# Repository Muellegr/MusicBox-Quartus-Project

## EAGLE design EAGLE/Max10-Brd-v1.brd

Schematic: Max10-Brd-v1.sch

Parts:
C1: 0.1uF; C0805
C2, C3: 4pF; C0805
C4, C15, C16, C32: 0.01uF; C0805
C5: 1nF; C0805
C6, C8, C11, C13: 10uF; C0805
C7, C9, C12, C14, C21, C24, C27, C30: 1uF; C0805
C10, C19, C22, C25, C28: 4.7uF; C0805
C17: 100uF; E5-6
C18: 1000uF; E3,5-10
C20, C23, C26, C29: 10nF; C0805
C31: 0.47uF; C0805
CB: 1uF; C0805
CI: 0.39uF; C0805
CS: 1uF Tant; C050-075X075
D1: DIODE-DO201-15; DO201-15
FB1, FB6: 220; M0805
FB2, FB3, FB4, FB5: 30; M0805
IC1: INA332AIDGKR; SOP65P490X110-8N
IC2: LM4991MAX_NOPB; SOIC127P600X175-8N
IC3: 10M50DAF484C7G; BGA484C100P22X22_2300X2300X200
IC5: IS42S16400J-7TLI; SOP80P1176X120-54N
IC6: CDCE937PWRG4; SOP65P640X120-20N
IC7: AD5320BRTZ; SOT95P280X145-6N
IC8: ADS7868IDBVR; SOT95P280X145-6N
IC9, IC10, IC11, IC12: MCP1726T-ADJE_SN; SOIC127P600X175-8N
IC13: REF3125AQDBZRQ1; SOT95P237X112-3N
IC14: LM2576HVS-ADJ; KTT0005B
J1: 1X2-3.5MM
J2, J14: CONN_05X2SHD; 2X5-SHROUDED
J3: CONN_20X2SHROUDED; 2X20_SHROUDED
J4, J5, J6, J7, J8: CONN_02; 1X02
J9, J10: CONN_01; 1X01
J11, J12, J13: CONN_03; 1X03
L1: 100uH; INDPM125125X650N
LED1: LED3MM
Q1: ELECTRET; 9.7ELECTRET
Q2: 24MHz; CTS406
R1, R2: 20k; M0805
R4, R5, R6: 2.2k; M0805
R8, R9, R10, R11, R12, R13, R14: 4.7k; M0805
R15, R16, R17: 18.2; M0805
R18, R19: 10k; M0805
R21: 1k; M0805
R22: 220; R0805
R23, R26: 510k; R0805
R24: 100k; R0805
R25: 150k; R0805
R27: 86k; R0805
R28: 12k; R0805
R29: 40k; R0805
R30: 20k; R0805
R31, R32: 0.4; M0805
TP$1: TEST_POINT
U$1: 2.1MMJACKTHM; PJ-102A
VR1: 10k; TRIMPOT-PTH-3386U

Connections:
ADC_CLK_10: IC3.N5 (IO_194), J13.3, R17.2
ADC_VREF: C6.1, C7.1, FB2.2, IC3.H6 (ADC_VREF)
AMP_MIC_OUT: IC1.6 (VOUT), IC8.3 (VIN), J10.1, R6.2
AUD_IN: C32.1, CI.2, IC7.1 (VOUT), J9.1
CS_N_ADC: IC3.W1 (IO_280), IC8.6 (CS), J12.1
DIN_DAC: IC3.E22 (IO_97), IC7.4 (DIN), J11.3
DRAM_ADDR0: IC3.U17 (IO_255), IC5.23 (A0)
DRAM_ADDR1: IC3.W19 (IO_298), IC5.24 (A1)
DRAM_ADDR2: IC3.V18 (IO_276), IC5.25 (A2)
DRAM_ADDR3: IC3.U18 (IO_256), IC5.26 (A3)
DRAM_ADDR4: IC3.U19 (IO_257), IC5.29 (A4)
DRAM_ADDR5: IC3.T18 (IO_242), IC5.30 (A5)
DRAM_ADDR6: IC3.T19 (IO_243), IC5.31 (A6)
DRAM_ADDR7: IC3.R18 (IO_234), IC5.32 (A7)
DRAM_ADDR8: IC3.P18 (IO_216), IC5.33 (A8)
DRAM_ADDR9: IC3.P19 (IO_217), IC5.34 (A9)
DRAM_ADDR10: IC3.R22 (IO_236), IC3.T20 (IO_244), IC5.22 (A10)
DRAM_ADDR11: IC3.P20 (IO_218), IC5.35 (A11)
DRAM_ADDR12: IC3.R20 (IO_235), IC5.36 (NC_1)
DRAM_BA0: IC3.T21 (IO_245), IC5.20 (BA0)
DRAM_BA1: IC3.T22 (IO_246), IC5.21 (BA1)
DRAM_CAS_N: IC3.U21 (IO_259), IC5.17 (!CAS), R10.2
DRAM_CKE: IC3.N22 (IO_203), IC5.37 (CKE), R12.2
DRAM_CLK: IC3.L14 (IO_171), IC5.38 (CLK)
DRAM_CS_N: IC3.U20 (IO_258), IC5.19 (!CS), R8.2
DRAM_DQ0: IC3.Y21 (IO_318), IC5.2 (DQ0)
DRAM_DQ1: IC3.Y20 (IO_317), IC5.4 (DQ1)
DRAM_DQ2: IC3.AA22 (IO_339), IC5.5 (DQ2)
DRAM_DQ3: IC3.AA21 (IO_338), IC5.7 (DQ3)
DRAM_DQ4: IC3.Y22 (IO_319), IC5.8 (DQ4)
DRAM_DQ5: IC3.W22 (IO_300), IC5.10 (DQ5)
DRAM_DQ6: IC3.W20 (IO_299), IC5.11 (DQ6)
DRAM_DQ7: IC3.V21 (IO_278), IC5.13 (DQ7)
DRAM_DQ8: IC3.P21 (IO_219), IC3.P22 (IO_220), IC5.42 (DQ8)
DRAM_DQ9: IC3.J22 (IO_151), IC5.44 (DQ9)
DRAM_DQ10: IC3.H21 (IO_135), IC5.45 (DQ10)
DRAM_DQ11: IC3.H22 (IO_136), IC5.47 (DQ11)
DRAM_DQ12: IC3.G22 (IO_121), IC5.48 (DQ12)
DRAM_DQ13: IC3.G20 (IO_120), IC5.50 (DQ13)
DRAM_DQ14: IC3.G19 (IO_119), IC5.51 (DQ14)
DRAM_DQ15: IC3.F22 (IO_112), IC5.53 (DQ15)
DRAM_LDQM: IC3.V22 (IO_279), IC5.15 (LDQM)
DRAM_RAS_N: IC3.U22 (IO_260), IC5.18 (!RAS), R9.2
DRAM_UDQM: IC3.J21 (IO_150), IC5.39 (UDQM)
DRAM_WE_N: IC3.V20 (IO_277), IC5.16 (!WE), R11.2
GND: C2.1, C3.1, C4.2, C5.2, C6.2, C7.2, C8.2, C9.2, C10.2, C11.2, C12.2, C13.2, C14.2, C15.2, C16.2, C17.-, C18.-, C19.2, C20.2, C21.2, C22.2, C23.2, C24.2, C25.2, C26.2, C27.2, C28.2, C29.2, C30.2, C31.2, C32.2, CB.2, CS.2, D1.A, IC1.2 (VIN-), IC1.4 (V-), IC1.8 (SHUTDOWN), IC2.1 (SHUTDOWN), IC2.7 (GND), IC3.A1 (GND_1), IC3.A22 (GND_2), IC3.AA4 (GND_55), IC3.AA18 (GND_56), IC3.AB1 (GND_57), IC3.AB22 (GND_58), IC3.B6 (GND_3), IC3.B9 (GND_4), IC3.B13 (GND_5), IC3.B18 (GND_6), IC3.D4 (GND_7), IC3.D11 (GND_8), IC3.D16 (GND_9), IC3.D20 (GND_10), IC3.E2 (GND_11), IC3.E5 (NC_1), IC3.E7 (GND_12), IC3.F6 (NC_2), IC3.F8 (IO_104), IC3.F10 (GND_13), IC3.F13 (GND_14), IC3.G5 (ANAIN1), IC3.G6 (GND_15), IC3.G8 (GND_16), IC3.G15 (GND_17), IC3.G18 (GND_18), IC3.G21 (GND_19), IC3.H5 (REFGND), IC3.J2 (GND_20), IC3.J5 (ANAIN2), IC3.J6 (GND_21), IC3.J16 (GND_22), IC3.J19 (GND_23), IC3.K3 (GND_24), IC3.K10 (GND_25), IC3.K12 (GND_26), IC3.L5 (GND_27), IC3.L13 (GND_28), IC3.L17 (GND_29), IC3.L21 (GND_30), IC3.M7 (GND_31), IC3.M10 (GND_32), IC3.M16 (GND_33), IC3.M19 (GND_34), IC3.N11 (GND_35), IC3.N13 (GND_36), IC3.P2 (GND_37), IC3.P6 (GND_38), IC3.P17 (GND_39), IC3.R19 (GND_40), IC3.R21 (GND_41), IC3.T4 (GND_42), IC3.T8 (GND_43), IC3.T14 (GND_44), IC3.T16 (GND_45), IC3.U10 (GND_46), IC3.U13 (GND_47), IC3.V2 (GND_48), IC3.V6 (GND_49), IC3.V19 (GND_50), IC3.W21 (GND_51), IC3.Y9 (GND_52), IC3.Y12 (GND_53), IC3.Y15 (GND_54), IC5.6 (GNDQ_1), IC5.12 (GND_1), IC5.28 (GND_2), IC5.41 (GND_3), IC5.46 (GNDQ_2), IC5.52 (GND_4), IC5.54 (GND_5), IC6.5 (GND_1), IC6.9 (GND_2), IC6.16 (GND_3), IC7.2 (GND), IC8.2 (GND), IC9.4 (GND), IC10.4 (GND), IC11.4 (GND), IC12.4 (GND), IC13.3 (GND), IC14.3 (GND_1), IC14.5 (!ON!/OFF), IC14.6 (GND_2), J2.2, J2.10, J4.2, J5.2, J6.2, J7.2, J8.2, LED1.K (C), Q1.- (1), R21.2, R24.1, R25.1, R28.1, R30.1, TP$1.TP1, U$1.RING, U$1.RING_SW, VR1.3 (CW)
GPIO_0: IC3.A2 (IO_1), J3.1
GPIO_1: IC3.A3 (IO_2), J3.2
GPIO_2: IC3.A4 (IO_3), J3.3
GPIO_3: IC3.A5 (IO_4), J3.4
GPIO_4: IC3.A6 (IO_5), J3.5
GPIO_5: IC3.A7 (IO_6), J3.6
GPIO_6: IC3.A8 (IO_7), J3.7
GPIO_7: IC3.A9 (IO_8), J3.8
GPIO_8: IC3.A10 (IO_9), J3.9
GPIO_9: IC3.A11 (IO_10), J3.10
GPIO_10: IC3.A12 (IO_11), J3.11
GPIO_11: IC3.A13 (IO_12), J3.12
GPIO_12: IC3.A14 (IO_13), J3.13
GPIO_13: IC3.A15 (IO_14), J3.14
GPIO_14: IC3.A16 (IO_15), J3.15
GPIO_15: IC3.A17 (IO_16), J3.16
GPIO_16: IC3.A18 (IO_17), J3.17
GPIO_17: IC3.A19 (IO_18), J3.18
GPIO_18: IC3.A20 (IO_19), J3.19
GPIO_19: IC3.A21 (IO_20), J3.20
GPIO_20: IC3.B1 (IO_21), J3.21
GPIO_21: IC3.B2 (IO_22), J3.22
GPIO_22: IC3.B3 (IO_23), J3.23
GPIO_23: IC3.B4 (IO_24), J3.24
GPIO_24: IC3.B5 (IO_25), J3.25
GPIO_25: IC3.B7 (IO_26), J3.26
GPIO_26: IC3.B8 (IO_27), J3.27
GPIO_27: IC3.B10 (IO_28), J3.28
GPIO_28: IC3.B11 (IO_29), J3.29
GPIO_29: IC3.B12 (IO_30), J3.30
GPIO_30: IC3.B14 (IO_31), J3.31
GPIO_31: IC3.B15 (IO_32), J3.32
GPIO_32: IC3.B16 (IO_33), J3.33
GPIO_33: IC3.B17 (IO_34), J3.34
GPIO_34: IC3.B19 (IO_35), J3.35
GPIO_35: IC3.B20 (IO_36), J3.36
GPIO_36: IC3.B21 (IO_37), J3.37
GPIO_37: IC3.B22 (IO_38), J3.38
GPIO_38: IC3.C1 (IO_39), J3.39
GPIO_39: IC3.C2 (IO_40), J3.40
GPIO_40: IC3.C14 (IO_52), J14.1
GPIO_41: IC3.C15 (IO_53), J14.2
GPIO_42: IC3.C16 (IO_54), J14.3
GPIO_43: IC3.C17 (IO_55), J14.4
GPIO_44: IC3.C18 (IO_56), J14.5
GPIO_45: IC3.C19 (IO_57), J14.6
GPIO_46: IC3.D15 (IO_73), J14.7
GPIO_47: IC3.D18 (IO_75), J14.8
GPIO_48: IC3.D19 (IO_76), J14.9
GPIO_49: IC3.E18 (IO_93), J14.10
MAX10_CLK1_50: IC3.P11 (IO_211), J13.1, R16.1
MAX10_CLK2_50: IC3.N14 (IO_197), J13.2, R15.1
unnamed: IC2.4 (-IN), R1.2, R2.1
unnamed: CI.1, R1.1
unnamed: IC6.14 (Y3), R17.1
unnamed: CB.1, IC2.2 (BYPASS), IC2.3 (+IN)
unnamed: IC2.5 (VO1), J1.2, R2.2
unnamed: IC2.8 (VO2), J1.1
unnamed: LED1.A, R22.2
unnamed: C1.1, Q1.+ (2), R4.1
unnamed: C1.2, VR1.1 (CCW)
unnamed: IC1.5 (REF), R5.1
unnamed: IC1.1 (RG), R5.2, R6.1
unnamed: IC9.7 (ADJ), R23.1, R24.2
unnamed: IC1.3 (VIN+), VR1.2 (WIPER)
unnamed: C2.2, IC6.1 (XIN/CLK), Q2.3 (2)
unnamed: C3.2, IC6.20 (XOUT), Q2.1
unnamed: IC6.19 (SDA/S1), R13.1
unnamed: IC6.18 (SCL/S2), R14.1
unnamed: IC6.7 (Y4), R15.2
unnamed: IC6.8 (Y5), R16.2
unnamed: FB1.1, IC6.6 (VDDOUT_1), IC6.10 (VDDOUT_2), IC6.13 (VDDOUT_3)
unnamed: D1.C, IC14.2 (OUTPUT), L1.1
unnamed: IC11.7 (ADJ), R27.1, R28.2
unnamed: C26.1, IC11.6 (CDELAY)
unnamed: IC12.7 (ADJ), R29.1, R30.2
unnamed: C29.1, IC12.6 (CDELAY)
unnamed: C23.1, IC10.6 (CDELAY)
unnamed: C20.1, IC9.6 (CDELAY)
unnamed: IC10.7 (ADJ), R25.2, R26.1
REF_VCC2P5: FB2.1, IC13.2 (OUT)
SCLK_ADC: IC3.AA1 (IO_320), IC8.4 (SCLK), J12.3
SCLK_DAC: IC3.D22 (IO_78), IC7.5 (SCLK), J11.2
SDO_ADC: IC3.Y1 (IO_301), IC8.5 (SDO), J12.2
SYNC_N_DAC: IC3.C22 (IO_60), IC7.6 (!SYNC), J11.1
TCK: IC3.G2 (IO_114), J2.1, R21.1
TDI: IC3.M5 (IO_181), J2.9
TDO: IC3.L4 (IO_168), J2.3, R19.2
TMS: IC3.H2 (IO_123), J2.5, R18.2
VCC1P2_VCC: C30.1, FB3.1, FB4.1, IC3.K11 (VCC_1), IC3.K13 (VCC_2), IC3.L10 (VCC_3), IC3.L11 (VCC_4), IC3.L12 (VCC_5), IC3.M11 (VCC_6), IC3.M12 (VCC_7), IC3.M13 (VCC_8), IC3.N10 (VCC_9), IC3.N12 (VCC_10), IC12.8 (VOUT), J8.1, R29.2
VCC1P2_VCCD: C10.1, FB4.2, IC3.G7 (VCCD_PLL3), IC3.G16 (VCCD_PLL2), IC3.T7 (VCCD_PLL1), IC3.U16 (VCCD_PLL4)
VCC1P2_VDDADC: C8.1, C9.1, FB3.2, IC3.J7 (VCCINT)
VCC1P8: C4.1, C5.1, C24.1, IC6.3 (VDD), IC10.8 (VOUT), J5.1, R26.2
VCC2P5: C21.1, IC3.F9 (VCCIO8_1), IC3.F11 (VCCIO8_2), IC3.G10 (VCCIO8_3), IC3.G11 (VCCIO8_4), IC3.K7 (VCCIO1A_1), IC3.L6 (VCCIO1A_2), IC3.L7 (VCCIO1B_1), IC3.M6 (VCCIO1B_2), IC9.8 (VOUT), J6.1, R18.1, R19.1, R23.2, R31.1
VCC2P5_CORE: FB5.1, FB6.1, R31.2
VCC2P5_VCCA: C11.1, C12.1, FB5.2, IC3.H8 (VCCA3), IC3.H15 (VCCA2), IC3.R8 (VCCA1), IC3.T15 (VCCA4)
VCC2P5_VCCADC: C13.1, C14.1, FB6.2, IC3.H7 (VCCA_ADC)
VCC3P3: C15.1, C27.1, FB1.2, IC3.F12 (VCCIO7_1), IC3.F14 (VCCIO7_2), IC3.G12 (VCCIO7_3), IC3.G13 (VCCIO7_4), IC3.G14 (VCCIO7_5), IC3.H16 (VCCIO6_1), IC3.J17 (VCCIO6_2), IC3.K16 (VCCIO6_3), IC3.K17 (VCCIO6_4), IC3.L16 (VCCIO6_5), IC3.M17 (VCCIO6_6), IC3.N6 (VCCIO2_1), IC3.N7 (VCCIO2_2), IC3.N16 (VCCIO5_1), IC3.N17 (VCCIO6_7), IC3.P7 (VCCIO2_3), IC3.P16 (VCCIO5_2), IC3.R6 (VCCIO2_4), IC3.R16 (VCCIO5_3), IC3.R17 (VCCIO5_4), IC3.T9 (VCCIO3_1), IC3.T10 (VCCIO3_2), IC3.T11 (VCCIO3_3), IC3.T12 (VCCIO4_1), IC3.T13 (VCCIO4_2), IC3.T17 (VCCIO5_5), IC3.U8 (VCCIO3_4), IC3.U9 (VCCIO3_5), IC3.U11 (VCCIO4_3), IC3.U12 (VCCIO4_4), IC3.U14 (VCCIO4_5), IC5.1 (VDD_1), IC5.3 (VDDQ_1), IC5.9 (VDDQ_2), IC5.14 (VDD_2), IC5.27 (VDD_3), IC5.43 (VDDQ_3), IC5.49 (VDDQ_4), IC8.1 (VDD), IC11.8 (VOUT), J2.4, J7.1, R8.1, R9.1, R10.1, R11.1, R12.1, R13.2, R14.2, R27.2, R32.1
VCC3P3_VCCA: C31.1, IC13.1 (IN), R32.2
VCC5: C16.1, C18.+, C19.1, C22.1, C25.1, C28.1, CS.1, IC1.7 (V+), IC2.6 (VDD), IC7.3 (VDD), IC9.1 (VIN_1), IC9.2 (VIN_2), IC9.3 (!SHDN), IC10.1 (VIN_1), IC10.2 (VIN_2), IC10.3 (!SHDN), IC11.1 (VIN_1), IC11.2 (VIN_2), IC11.3 (!SHDN), IC12.1 (VIN_1), IC12.2 (VIN_2), IC12.3 (!SHDN), IC14.4 (FEEDBACK), J4.1, L1.2, R4.2, R22.1
VCC9: C17.+, IC14.1 (VIN), U$1.TIP

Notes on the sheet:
Speaker Ouput Expected: 8 ohm/3W capable
Audio In
Shutdown Pin Active high that turns off the chip
Speaker Output Block-v1
Tristan Luther ECE342: Junior Design Music Group 01
Microphone Input Block-v1
Gain Equation: G = 5 + 5(R6/R5)
Amplified out of microphone to go to ADC
Nancy Morales ECE342: Junior Design Music Group 01
SDRAM Block-v1
NOTICE: DRAM_ADDR12 was added for backwards compatability with the older SDRAM chip for the DE-10 (32MX16). Otherwise not attached
JTAG Interface-v1
PLL Clock Div-v1
Default: I2C Address 0xDA/0xDB
Noise Suppresion-v1'
GPIO Pins-v1
DAC/ADC-v1
ADC
DAC
5V Regulator
2.5V Regulator
1.8V Regulator
5V, 1P8V, 2P5V
3P3V, 1P2V
3.3V Regulator
1.2V Regulator
Debugging Header

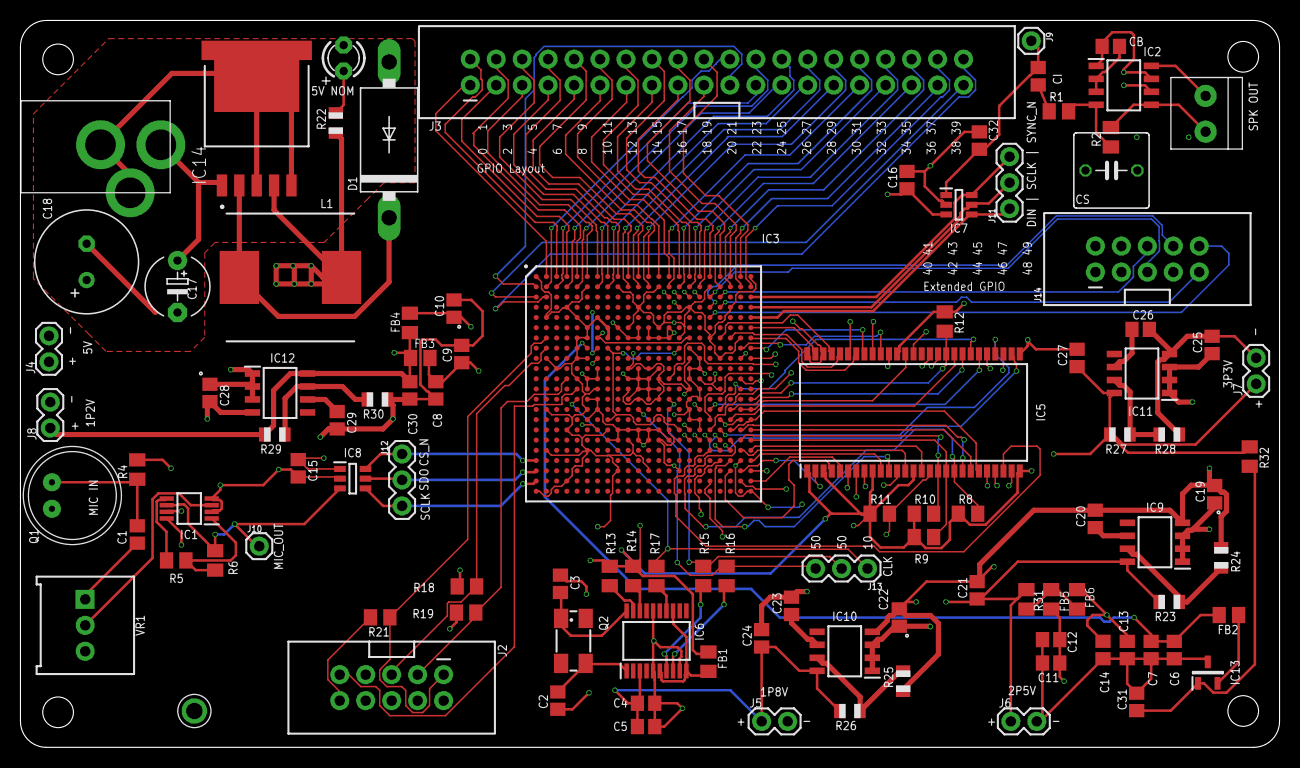
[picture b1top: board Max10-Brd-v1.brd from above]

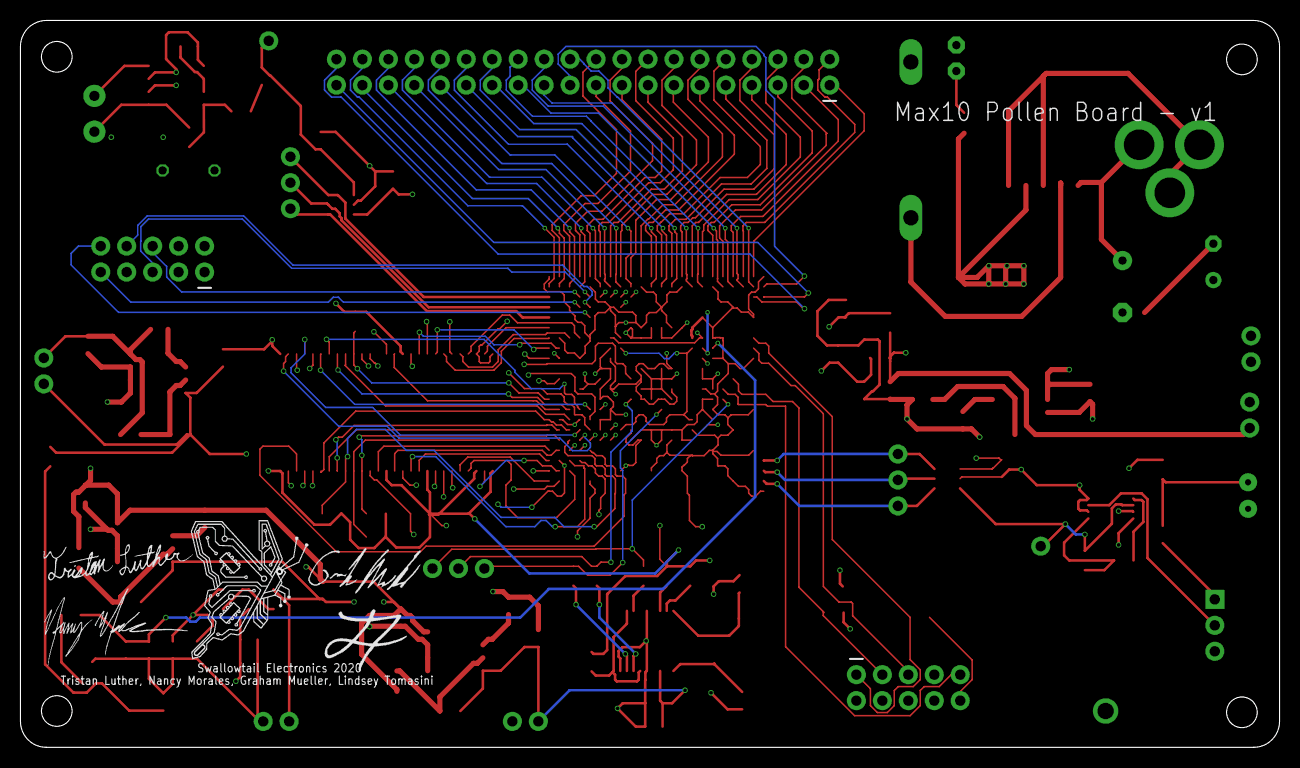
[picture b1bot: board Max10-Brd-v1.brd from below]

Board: 4 copper layers, 123.2 x 71.1 mm, 110 parts (4 on the bottom side), 147 nets.

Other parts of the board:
U$2: GRAHAM_SIGNATURE_BPLACE
U$3: NANCY_SIGNATURE_BPLACE
U$4: LINDSEY_SIGNATURE_BPLACE
U$5: TRISTAN_SIGNATURE_BPLACE
U$6: SWALLOWTAIL_NO_TEXT_BACK

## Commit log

2020-01-23 Initial Project Upload
2020-01-23 Removing old project
2020-01-23 Small basic update
2020-01-23 Created more formal pin naming for the DE10 Lite board
2020-01-23 Added 10 input pins
2020-01-25 Updated IO settings
2020-01-25 Corrected some pin naming & voltages.
2020-01-25 Added input smoothing module. <0.001s begins to see unsmoothed values.
    Added smoothing to all input pins. These are now designated by _s for _smoothing.
2020-01-25 Basic state machine with a single state added. When Play Song 0 is pressed, it enters state 1.
2020-01-25 UI State machine extended slightly. Next step is adding logic to what each state is doing. This will be performed with a basic self counting clock and a "finish" signal, telling the state to return t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
2020-01-26 Preparation for new branch
2020-01-26 Added basic music keys. These only operate in the do nothing stage and make recording stage. They are currently configured to light LEDs up.
2020-01-26 Added utility function ClockGenerator. This divides a clock. A formula is included for this.
    I generated 2 clocks (1Khz & 1Hz) and 1hz matched a clock well for 10 seconds.
2020-01-26 Added Play Song 0 module that returns automatically to Do Nothing after 5 seconds.
2020-01-26 Added other base states as individual modules.
    At this stage, all UI can be interacted with. Pressing a button causes it to enter that state and ignore further UI. Music keys light up LEDs only when they are allowed to (nothing & make recording s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
    Added comments.
2020-01-26 Dummy commit.
2020-01-27 No change
2020-01-27 Write a untested SPI output meant for the specific dac used. Next step will be to test this in ModelSim and verify it is timed correctly as well as sending the correct bits as expected. Finally, the 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
2020-01-28 Added temporary modelsim for simulating the SPI output.
2020-01-28 Organized modelsim folder.
2020-01-29 SPI connected to power board but not getitng results. Seems as if it is off. Extended sync low time to ensure we are ending it properly.
2020-01-31 Still in testing setup, but correctly sending data to DAC. Currently performs a buzz saw output as it counts up over 4 seconds.
2020-02-04 SPI Output complete. Currently configured as a test setup where it sends a linear increasing output signal to the DAC.
2020-02-04 ModelSim commit
2020-02-04 Oups forgot to check out branch. These are meant for SPI IO.
2020-02-04 Worthless files?
2020-02-04 Added ADC SPI Input Verified working in ModelSim.
2020-02-04 ModelSim more like wet noodle sim
2020-02-04 Modelsim would be an excellent vacuumn.
2020-02-06 Small notes added
2020-02-08 Added comments to the main files a bit.
2020-02-09 Added python function that generates precalculated sine values. Frequency generator uses these now. Very compact. Next step will be to have frequency input that controls rate of indexing.
2020-02-09 Signal generator complete but not tested. Currently hooked up to lights. Switches increase rate at which the sine value is shown on the LEDs. More switches up == faster frequency.
2020-02-09 Fixed some values to be correctly sized. 1 might now be 16'd1 for example. This eliminates a lot of the error messages.
2020-02-10 1 signal generator outputs to DAC and shows up correctly on oscilloscope. System works at correct frequency. Unsure how it will sound at high frequencies.
2020-02-11 Pull Request Test
2020-02-11 Stage test for issue tracker.
2020-02-11 Another test. fixed #7
2020-02-11 Added raw SDRAM_Controller file. Is not expected to work at this point.
2020-02-11 Added some comments to the SDRAM controller. Moved stuff around, should be a little easier to read.
2020-02-12 Added module to main file however this is not tested. Added supporting segment display driver. This is untested but is expected to work. Enables displaying a value stored in 20 bits to the display.
2020-02-12 Added PLL that generates a 143Mhz clock. This is neccesary for the SDRAM to work at that speed.
2020-02-13 Added RGB Block Code
    Added the RGB block code including the RGB LED driver, a tone genrator (basic pwm), a button debouncer, and a test banch for testing.
2020-02-13 Added VS Code support.
2020-02-14 Pointless stage, edited some spaces.
2020-02-14 Added multiple frequencies that sum into a single frequency that plays with sliders. Proof of concept test.
2020-02-15 SDRAM test not working. Loading some older SDRAM files as the older SDRAM repository test passes.
2020-02-15 SDRAM now passes test after assigning SDRAM controller proper input.
2020-02-16 Testing version. Make and Play record a constant value across 5s to test record and retrieve.
2020-02-17 Small changes and notes.
2020-02-17 Lame update since git isn't letting me revert.
2020-02-17 Sometimes git gets stupid. This is a pull request. ADC is connected to Record mode, where it writes 22Khz to memory for 5 seconds. Play mode retrieves from memory and has the output value available b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
2020-02-18 Fixed errors related to multiplication and division. Quartus prime really loves turning things into a float value, while offering no realistic way to return to an integer easily. This goes against th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
    Added function that enables applying an amplitude multiplication with a signal. It is now easy to do 'volume control' on a signal.
    This signal can be applied to multiple signals and added together for signal addition.
    +Added triangle waveform. This will assist sound key playing by offering a more unique sou
2020-02-18 Cleaned up main document and signal generators.
    This is untested at high speeds.
2020-02-18 Added easier testing setup for signals. Value sent to dac now displayed on segment display.
2020-02-18 I think my FPGA went clabooey? DAC started misbehaving for a few seconds and now is not responding.
    My DAC clock is weirdly shaped now. Maybe the pin itself went bad?
2020-02-19 FPGA cool, it's the clock pin going to DAC that's weirdin it up. I think it needs a decoupler. Using a female-female with a power cable seems to fix it.
    Some adjustments made to timing. Orignally calculated things based off a pure 50MHz clock, in reality that clock is slightly fast.
    Downshifted 32KHz clock (determines frequency). Output frequency is with square waves is correct at 1KHz, but drifts around. Seems to pass +/- 4% rule.
2020-02-20 Adjusted timing in square signal generator. It was possible for it to overshoot - I'm not sure what the behaviour of this would be. It would also lose an increment when it overshot when it was reset 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
    Fixed this by having a modulo function on the division part, and also increment the counter when it has overshot.
    So every clock cycle it not only increments, but when it's dividied it should not exceed 32k.
2020-02-20 Oups, better format included.
2020-02-20 Continued playing with signal.
    32KHz signal is right on the dog.
    Signals are now much closer.
    Final issue is harmonics caused by the counter. This increments every 32K a second. There is a small delay makes it hard for oscilloscope to count frequency.
    5000Hz -> 4500~~ (jumps a lot)
    1320 Hz -> 1333Hz
    600Hz -> 594 to 603, mostly 603
2020-02-20 Updated signal generator triangle to include updated timing values. Making pull request back to main.
2020-02-20 Ignored .db folder. Should have done that a long while ago.
2020-02-21 Cleaned some mild comments. Code is still based on the previous pull that was apart of the signal combiner testing branch.
    Added file ignores so commits are a little cleaner.
2020-02-25 Found a working script that gives me what I need. Need to expand on it and flesh it out to fully suit my needs.
2020-02-25 Small progress to this. Now lists acutal frequencies every 0.1 seconds!
2020-02-25 Performs FFT on song, splits it up and assigns values to array. Sitting at a point where I can write values to files that I will need. I have frequency and correct amplitude.
2020-02-26 Output goes to speaker. Doesn't sound great but is close.
2020-02-26 Song0 setup to play a song from start to end with 3 frequencies and an update rate of 0.05s. It plays the correct frequency, but it sounds off. There's a variety of reasons for this. DAC no low pass 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
    It may help to simulate these at higher frequencies instead of 32k.
2020-02-26 Added ROM Testing
    Added files for storing a SINE into ROM and reading it out to thr SPI DAC. REQUIRES HARDWARE TESTING.
2020-02-27 Added basic todo and removed some old commented code.
    Next step will begin ensuring things are connected and then fleshing out major parts.
2020-02-28 Updated state controller and make recording to include SPI input sample value.
2020-02-28 Added bee mode pin and basic control. Added button toggle.
2020-02-29 Updated signal generator to include the amplitude as part of the main module. This helps simplify interfaces. Updated triangle and square wave to the style of Sine which was the current up to date ve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
2020-02-29 +Updated 7 segment display to no longer fill in leading zeroes. This also helped optimize it for the compiler. Segment display is a little cleaner. +Tested UI toggle button for bee mode. Works. +Test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
2020-02-29 Added new pinout scheme that makes more sense. Added LED output for MIDI keys and music keys. these are currently disconnected.
2020-02-29 lol forgot to save file
2020-02-29 Added music key functionality. Each key has a unique frequency and some have some more advanced freq playback to show off what it can do. Music keys have a WIP volume falloff. It starts at 255 when f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
2020-03-01 Preparing Arduino IDE integration
2020-03-02 Added Arduino_SPI input for FFT integration. This is not fully implemented and is awaiting testing.
2020-03-02 Fixed massive and detromental numbering issue introduced by soon to be prior group member.
2020-03-02 Added LED controller. All leds should be on at half brightness. Mode keys connected to green LED, however the actual color will be determined b the physical LED chosen.
2020-03-03 Create de10fft.ino
    ATmega code for reporting the FFT Data and sending over SPI
2020-03-03 Added very basic light module that should allow interaction with panel lights. Currently mostly untested.
2020-03-04 SPI working in it's initial stage. Communicates with arduino. Poor method means we only recieve 14 bits. Initial setup of ROM and song0 & 1 setup.
2020-03-04 Added Python ROM Generator/Piano Tone SPI
    More support scripts to get music playing in ROM and getttign correct tones.
2020-03-04 End of Rom testing for now. reverting to simplier times.
2020-03-04 Last working example
2020-03-05 EAGLE Files and Head Banging
    EAGLE Files and BOM for those interested.
2020-03-06 System verification build. 265/300. Big problems were lack of microphone for full system integration.
2020-03-06 Cleaned up files and removed old comments. No changes.
2020-03-09 Reupload Arduino FFT, Fix ROM script bug, Guide for Audacity
    Improvments for project
2020-03-09 Oddball commit : Previous commits were NOT happy with something and giving compile errors. This should have all the major changes from Tristan.
2020-03-09 ROM is currently sending correct values to the segment display.
2020-03-09 Update MusicBoxROM.py
    Bug fix
2020-03-10 Rom is a bust, will use for bee noise only.
    SPI is not working. Display is hooked up to the current value being shifted in. LED 4 is clock, LED 5 is chip select, LED6 is data.
    It looks like data is just never arriving.
2020-03-11 Nearing end of project. Currently all completed features work. Song1 sounds bad.
2020-03-12 Final submission.

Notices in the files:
parts and their libraries:
SparkFun-Resistors: Licensing: Creative Commons ShareAlike 4.0 International - https://creativecommons.org/licenses/by-sa/4.0
